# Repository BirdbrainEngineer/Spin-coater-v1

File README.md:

# Birbrain's DIY Spin Coater version 1
This repository contains the source code for a diy spin coater I designed. A video on YouTube showing some of the design- and build process of this device can be found [here](https://www.youtube.com/watch?v=mm2ZiJNfISs). 

### What is it?
 A spin coater is a tool used for depositing thin films of liquids onto a substrate. Usually the liquid is a solution of a relatively quickly evaporating solvent and the coating solute. The phantom force of centrifugal force causes any liquids to travel radially outwards on the substrate. However, due to surface tension, viscocity and other phenomena, some of the solution sticks to the substrate. The solvent from the thin layer of solution then evaporates, leaving behind a thin film of the solute. Using this technique, it is possible to obtain film thicknesses as small as a couple-dozen nanometers!
 
  So... in a nutshell, a spin coater is essentially just a controllable/programmable spinner onto which one can attach a variety of substrates. 
 
### Why?
 Due to the insane simplicity of this device, one would imagine that such tools would be rather cheap and easy to aquire... However, because usually these devices are used in universities and research laboratories, then unfortunately one can expect a markup in the hundreds, to sometimes thousands of percentage points!!! This is just pure insanity, and because I like building some of my own tools, I decided to design and build my own simple spin coater.

 Above is a photo showing thin-film-interference on a coated first-surface mirror(definitely not optical quality haha). The coating solvent was acetone and solute was acrylic, which is a very challenging mix to work with... hence the somewhat sub-par result. 

### Is this project going to be maintained? 
 Don't hold your breath for it! I may upload a few bug fixes if and when they pop up as I work with my spin coater, but I do not intend to improve this version much if at all. There is a likelyhood that a few years from now, I will build a yet more advanced version- a spin coater of laboratory quality for projects that require utmost precision. 

### What is needed to build this project?
The spinner hardware is controlled by a Raspberry-Pi Pico(just Pico from here on), a cheap microcontroller that sits between an Arduino and ESP32 in its processing power. The speed of the Pico as well as its powerful hardware-PWM capabilities are the reason for me picking the Pico for this project.

Multiple extremely important parts of the device, such as the hub and sample holder combo that makes up the gravity chuck design of this spin coater, are meant to be 3d-printed. So, it is basically a necessity to have access to a basic 3d printer... or a cnc mill if going overkill. 

Because I did not make a PCB design for the logic board for this project, then you'll also need access to a soldering station.

And of course, a PC of some sort to be able to compile- and upload the firmware onto the Pico. More on software at [software setup](#software-setup) paragraph of this document.

The list of parts along with their approximate cost can be found at [bill of materials](#bill-of-materials) section of this document. 

## Software setup
This project uses [PlatformIO](https://platformio.org/) with [Visual Studio Code](https://code.visualstudio.com/)(VSCode) IDE. This near-trivializes certain aspects of programming for the Pico. In addition, this project uses the "earlephilhower" Arduino-pico core (see platformio.ini). For these reasons, as far as I am aware, the code is not possible to compile with any other setup, and even if it is possible, I recommend VSCode with PlatformIO anyways. Because the code uses a couple external libraries that PlatformIO normally manages, then it is necessary to have an Internet connection while dealing with this code. 

Getting the firmware for the Pico running should be as simple as these three steps. 

1. Clone the repository to your desired location and open the project in VSCode.
2. Connect the pico to your machine over a usb cable, while holding down the "BOOTSEL" button on the Pico. Release the BOOTSEL button after the Pico is connected.
3. Click "Build" and then "Upload" in VSCode, or just "Upload"(this should automatically build the project). The firmware should then be compiled and uploaded to the Pico. Once VSCode signals to you that the upload is complete, simply unplug the USB from the Pico and on the next power-up of the Pico, it should execute the code of the firmware.

Granted that the rest of the surrounding hardware has been built and set up correctly, the spin coater should just simply work. Surrounding hardware specification can be found under the "[Hardware design](#hardware-design)" paragraph of this document.

## Bill of materials
The prices in the bill of materials are approximate prices of the components that I could quickly find at the time of publishing of this document. These prices are most certainly subject to change over time.

* Anything in brackets is the particular size/component I used.
* Price is for the full amount (eg. 2$ for a component that has 4 stated in the amount, means each component costs 0.50$). 

| Amount | Component                                    | Price  |
|--------|----------------------------------------------|--------|
| 1      | Raspberry Pi Pico                            | 5$     |
| 1      | 80mm 4-pin PC fan (Arctic P8 Max)            | 10$    |
| 1      | 12V, 1A, power adapter with barrel connector | 5$     |
| 1      | SPI micro-SD-card reader module              | 3$     |
| 1      | 16x2 LCD display module                      | 4$     |
| 1      | 4x4 membrane keypad                          | 5$     |
| 1      | 15x21mm KCD1 power switch                    | 1$     |
| 1      | Suitable DC-005 barrel jack (5.5x2.1mm)      | 1$     |
| 4      | Suitable anti-slip rubber furniture leg      | 2$     |
| 1      | 25x (empty) cd/dvd spindle                   | 3$/10$ |
| 2      | WH148 10K potentiometer                      | 2$     |
| 2      | WH148 potentiometer knob                     | 2$     |
| 2      | PT15 10K potentiometer or equivalent         | 0.50$  |
| 12     | 3mm M3 heat set insert                       | 1$     |
| 4      | 4mm M4 heat set insert                       | 1$     |
| 2      | TO220 heatsinks                              | 1$     |
| 16     | M3 10mm screw                                | 0.50$  |
| 4      | M4 20mm or 17mm screw*                       | 0.50$  |
| 1      | 12x8cm prototyping/perf board                | 0.50$  |
| 1      | 1A glass tube fuse                           | 0.50$  |
| 1      | glass tube fuse holder                       | 0.50$  |
| 1      | 1N5819 schottky diode or equivalent          | 0.50$  |
| 5      | 1N4005 diode or equivalent                   | 1$     |
| 2      | 3mm round LED, different colors              | 0.50$  |
| 6      | resistors: 1x1K, 1x4K7, 1x6K8, 2x10K, 1x68K  | 0.50$  |
| 4      | 100nF ceramic capacitor                      | 0.50$  |
| 1      | 330nF 15V+ capacitor(I used 1x100nF, 1x100uF)| 0.50$  |
| 2      | 100uF 15V+ electrolytic capacitor            | 0.50$  |
| 2      | 2N2222A transistor or equivalent             | 0.50$  |
| 1      | F9540N transistor or equivalent              | 1$     |
| 1      | L7805CV voltage regulator                    | 1$     |
| -      | Preferred connectors & wiring for soldering  | ~5$    |
| -      | ~235g of PLA filament                        | 7$     |
| -      | ~42g of PETG filament                        | 1.50$  |

* Total: ~69$

## Hardware design

* Parts with a "*" are technically optional, but recommended. LED-s following a resistor with a * are optional in the same manner. 
* Q3 transistor in the schematic is a BC547A, however this can be replaced with a 2N2222A or equivalent. BC547A is an old and deprecated NPN BJT. The reason why I used it is to have a slower signal fall time (yes, really), which helps to make the PWM duty-cycle look more like what the Pico outputs. With a 2N2222A transistor, the PWM duty cycle to the fan motor is shorter than what the Pico outputs. Technically it should be fine as the PID control loop should be able to compensate.
* R5 & R6 are PT15 type potentiometers. R7 & R8 are WH148 type potentiometers.
* All 1N4005 diodes could technically be replaced by 1N5819 schottky diodes, but should not be necessary. 
* C3 capacity comes from the datasheet for L7805CV, however it does appear that the capacity can be larger. Probably the more important thing is that at least some of the capacity is quick-acting, eg. ceramic capacitors. 

### Some notes on the design...
If you would prefer to use a KiCAD schematic, then one has been produced and tested by @krasimirk. It can be found in the [BirdbrainSpinCoaterPCB_v1.1 directory](Hardware/BirdbrainSpinCoaterPCB_v1.1).

Make sure to install a TO-220 heatsink at least on the L7805CV, it will burn out otherwise. A heatsink on the F9540N is technically not needed, but optional.

One might notice that the 16x2 LCD display is directly interfaced with the Pico, even though the LCD display is running off 5V. This is safe to do as long as RW is tied to ground, guaranteeing that the display only ever gets written to. In such a case, the Pico's 3.3V should be enough to count as a logical high while transmitting data. 

## Spinner usage
If you have built yourself a spin coater of this design and firmware then here's a rundown of what can be found in the menu system of the spinner and what the different options do. 

### Keys
By default the keymapping for the spin coater when using the default 4x4 membrane keypad is as follows:

* Numerics - Correspond to the corresponding number. 
* `*` - Backspace / Exit.
* `#` - Enter / OK.
* `A` - YES, if a question prompt appears; Otherwise the letter A.
* `B` - NO, if a question prompt appears; Otherwise the letter B.
* `C` - UP, if navigating the menus; Otherwise the letter C.
* `D` - DOWN, if navigating the menus; Decimal dot/period ( `.` ), if entering a fractional number; Otherwise the letter D. 

### Booting
*For a painless first boot of the spin coater, make sure to copy the contents of the "Spinner Memory Image" folder onto a clean SD card. Ideally the SD card has a relatively small memory size.*

During booting, the spin coater checks for whether an SD card can be found on the default SPI pins. If not, then the spin coater will enter [memoryless operation](#memoryless-operation), and notifies the user of this occuring. The menu should then appear and the spin coater is ready for use in memoryless operation mode. 

If the SD card is present, then next the spin coater will check whether a `JOBS` folder exists in the root directory of the SD card. If not, one will be created automatically. If the `JOBS` folder exists, then the spin coater will attempt to load any jobs in the folder. The `JOBS` folder should contain *only* job files. [Job files](#job-file-structure) are extensionless JSON files with a very specific structure. Errors during this phase of booting could end up being unrecoverable AND recurring. If this is the case, the spin coater should be shut down, after which the SD card has to be removed from the spin coater and the files inspected at a PC. Any job files that have been saved incorrectly should be deleted from the folder. The spin coater should be able to boot again after doing so. 

Next the spin coater will attempt to locate the PID test job file called `PID` in the root directory. If this job is not found or is corrupted, then the spin coater will not be able to use the "PID test" functionality. In case of this happening and the user still wanting to use the PID test functionality, the user should shut down the spin coater, then remove the SD card from the spin coater and inspect the files at a PC. If a file called `PID` exists in the root directory then the integrity of the file should be checked, or alternatively a new PID test job file should replace the corrupted one. If the file is missing then a job has to be created/copied, and the file renamed to `PID`. 

### Normal operation
* `1/5: Quick start`
    * `1/2: Programmed` - Opens up a standard [job routine creation](#job-routine-creation) dialouge. After the dialouge has been finished, asks whether to run the job or not. If answered affirmatively, then executes the programmed job routine. After the routine has finished, asks whether to run the job again or not. If answered affirmatively, runs the job again. Otherwise asks whether to store the job permanently. If answered affirmatively, then a job name can be entered and the job routine will be saved as a job that can be interacted with through the `Jobs` menu.  
    * `2/2: Analog` - Gives direct control over the spinner to the user. The speed can be adjusted using the "coarse" and "fine" potentiometers. Coarse control spans from 0% to 90% of maximum spinner speed. Fine control spans a 10% range that gets added ontop of the current coarse control. Eg. if coarse control is set to 38% and fine control to 4%, then the output speed will be 42% of the maximum spinner speed. **WARNING: When exiting analog control mode, the spinner spins up to a slow speed for a few seconds, even if the spinner is already stationary!**
* `2/5: Jobs`
    * `1/3: Load job` - Opens a list of jobs currently stored on the SD card. The specific job can be searched in the menu, or by using the `Search for a job` function. If the job search turns up positive or the specific job is chosen from the menu, the spin coater asks whether to run the job. If answered affirmatively, performs the job routine. 
    * `2/3: Create job` - First asks to enter the new job routine's name. If a job with the specified name already exists, then offers to enter a different name or delete the job with the specified name. Once a suitable name is chosen, the spin coater asks to confirm the name, after which the standard [job routine creation](#job-routine-creation) dialouge is opened. After the job routine is finished, the job is saved on the SD card. If the user decided to override a previous job, then the previous job with the same name is deleted before the new job is saved. 
    * `3/3: Delete job` - Opens a list of jobs stored on the SD card. The specific job the user wishes to delete can be searched in the menu, or by using the `Search for a job` function. When answered affirmatively to whether to really delete the specified job, the job is removed deleted from the SD card. **As it stands right now, the "Search for a job" option is rather buggy, so it is not recommended to use it!**
* `3/5: Test`
    * `1/2: Spinner params.` - Spinner parameters test is a rudimentary test to find out some basic parameters of the spinner. The test consists of a speed- and acceleration tests. The speed test finds out the minimum and maximum speed of the spinner, as well as the minimum duty cycle length to make the spinner spin. The acceleration test tests the maximum acceleration and deceleration three times in a row, and then averages the results. The results from the tests are then displayed to the user to create their job routines accordingly. The minimum duty cycle speed will not be reported to the user but the spin coater's configuration is updated accordingly. **Please note that since the very first test is finding out the minimum duty cycle of the spinner, it may look like nothing is happening for a while. Rest assured, the controller is simply creeping up on the minimum duty cycle.**
    * `2/2: PID` - PID test is a rudimentary test to gauge whether the current PID constants are performing acceptably. The routine of this test can be changed by manually replacing the job file named `PID` in the root directory on the SD card. 
* `4/5: Calibration`
    * `1/6: Set Kp` - Displays the currently set P (proportional) constant of the PID controller. If no numeric value is entered, the constant remains unchanged, otherwise new number is set as the new value of the constant. The configuration of the spin coater is also updated so on next "normal operation" boot the constant is retained. 
    * `2/6: Set Ki` - Displays the currently set I (integral) constant of the PID controller. If no numeric value is entered, the constant remains unchanged, otherwise new number is set as the new value of the constant. The configuration of the spin coater is also updated so on next "normal operation" boot the constant is retained. 
    * `3/6: Set Kd` - Displays the currently set D (derivative) constant of the PID controller. If no numeric value is entered, the constant remains unchanged, otherwise new number is set as the new value of the constant. The configuration of the spin coater is also updated so on next "normal operation" boot the constant is retained. 
    * `4/6: Min duty cycle` - Updates the configuration of the spin coater to reflect the new minimum duty cycle value obtained during the last "Spinner parameters" test. Effect is immediate.
    * `5/6: Analog-in alpha` - Allows for adjusting the alpha of the exponential average for the analog control potentiometer readings. Should be a value between `0` and `1` (default is `0.01`). Smaller values mean the average, and therefore the whole reading of the potentiometers moves slower, but noise in the readings is suppressed. **Changing this value is unlikely to be needed.**
    * `6/6 RPM alpha` - Allows for adjusting the alpha of the exponential average for the RPM readings. Should be a value between `0` and `1`(default is `0.2`). Smaller values mean the average, and therefore the whole reading of the potentiometers moves slower, but noise in the readings is suppressed. **Changing this value is unlikely to be needed.**
* `5/5: Information`
    * `1/3: Device info.` - Device information contains the current revision of the firmware and hardware, programmer names/handles and hardware developer names/handles, as well as the software- and hardware license identifiers.
    * `2/3: HARDWARE LICENSE` - Embedded license identifier and link for more information about the Creative Commons 4.0 Attribution-ShareAlike license.
    * `3/3: SOFTWARE LICENSE` - Embedded MIT license.

### Memoryless operation
In memoryless operation mode the spin coater is not able to execute any functionality that has to do with accessing the memory, naturally. 

If `Programmed` is chosen from first menu option `Quick start`, then the spin coater will not offer to save the created set of instructions as a job when exiting the `Programmed` mode. 

The second menu option `Jobs` is completely non-functional. 

The "PID test" under third menu option `Test` is not available.

All spinner configuration will have reverted back to firmware defaults. It is possible to update the configuration, however if the spin coater is shut down, all changes made are lost.

## Building your own
If you would like to build your own spin coater of this design, then the [assembly manual](https://birdbrain.engineer/spin-coater/instructions/) can be found in the **Instructions** folder of this repository.

## Licenses
The software of this project is licensed under [MIT](https://opensource.org/license/mit/) software license.

The hardware design of this project is licensed under [Creative Commons 4.0 Attribution-ShareAlike](https://creativecommons.org/licenses/by-sa/4.0/deed.en) license.

## Job routine creation

When creating a job routine in the spinner, the spinner will ask the following three questions in a loop.

1. **Which task to perform** 
    
    * *Ramp* - Performs a linear ramp-up or ramp-down of the speed of the spinner.
    * *Hold* - Holds the spinner speed at a specified speed.
    * *End* - Final instruction in a job routine, if this is encountered, the job routine is immediately stopped and finished.

2. **RPM / Speed**
    
    If the task was to "ramp", then it will linearly interpolate towards this speed from the previously set speed (0 if first task in the routine). If the task was "hold", then sets the speed setpoint to this speed. No effect if any other task is encountered.

3. **Duration**

    The duration of the particular task in the routine in **milliseconds**. In case of "ramp" task, the speed is interpolated over the course of this time duration. In case of "hold" task, the speed is set and held for this time duration. No effect if any other task is encountered.

Once the `End` task is chosen while programming a job routine, the spin coater will immediately assume the job routine finished and so the programming interface is exited.

For example, if the following commands are entered while programming:

* Ramp, 3000, 5000
* Hold, 3000, 5000
* Ramp, 500, 6000
* End

... then when the job gets executed, the spin coater would linearly spin the spinner from 0 RPM up to 3000RPM over the course of 5 seconds. It would then hold the speed at 3000RPM for a further 5 seconds. Finally, it would linearly slow down the spinner from 3000RPM to 500RPM over the course of 6 seconds. The job would then immediately finish. 

## Job file structure
Job files are [JSON](https://www.json.org/json-en.html) files with no `.json` extension.

To have the spin coater load your job files, they need to be placed into the `JOBS` folder which should be found in the root directory of the SD card. The only exception to this is the job file called `PID`, which is used for the PID test. The `PID` job should be found in the root directory of the SD card.

The following is a sample job file.

The job file has 5 single-valued variables and a single array.

* `length` is an integer that **must** be equal to the number of elements in the `sequence` array.
* `use_embedded_pid_constants` is a boolean which specifies whether to use the `Kp`, `Ki` and `Kd` values baked into the job file as PID constants for the PID controller, or whether to use the spinner's currently set internal PID constants. `false` means that the spinner's internal PID constants are used instead of the constants specified in the file.
* `Kp` is a floating point number that will be used as the **Kp** constant for the PID controller if `use_embedded_pid_constants` is set to `true`. 
* `Ki` is a floating point number that will be used as the **Ki** constant for the PID controller if `use_embedded_pid_constants` is set to `true`. 
* `Kd` is a floating point number that will be used as the **Kd** constant for the PID controller if `use_embedded_pid_constants` is set to `true`. 
* `sequence` is an array type which holds elements made of three variables:
    * `duration` is an integer. Refer to [job routine creation](#job-routine-creation) for more information.
    * `task` is an integer. `1` means "hold" task, `2` means "ramp" task and `3` means "end" task. No other numbers should be used here. Refer to [job routine creation](#job-routine-creation) for more information.
    * `rpm` is an integer. Refer to [job routine creation](#job-routine-creation) for more information.

## Known bugs
* The `Search for a job` functionality under `Delete job` menu does not work properly if the name contains numbers. **Workaround:** Find the job you wish to delete in the `Delete job` menu manually and delete it that way.

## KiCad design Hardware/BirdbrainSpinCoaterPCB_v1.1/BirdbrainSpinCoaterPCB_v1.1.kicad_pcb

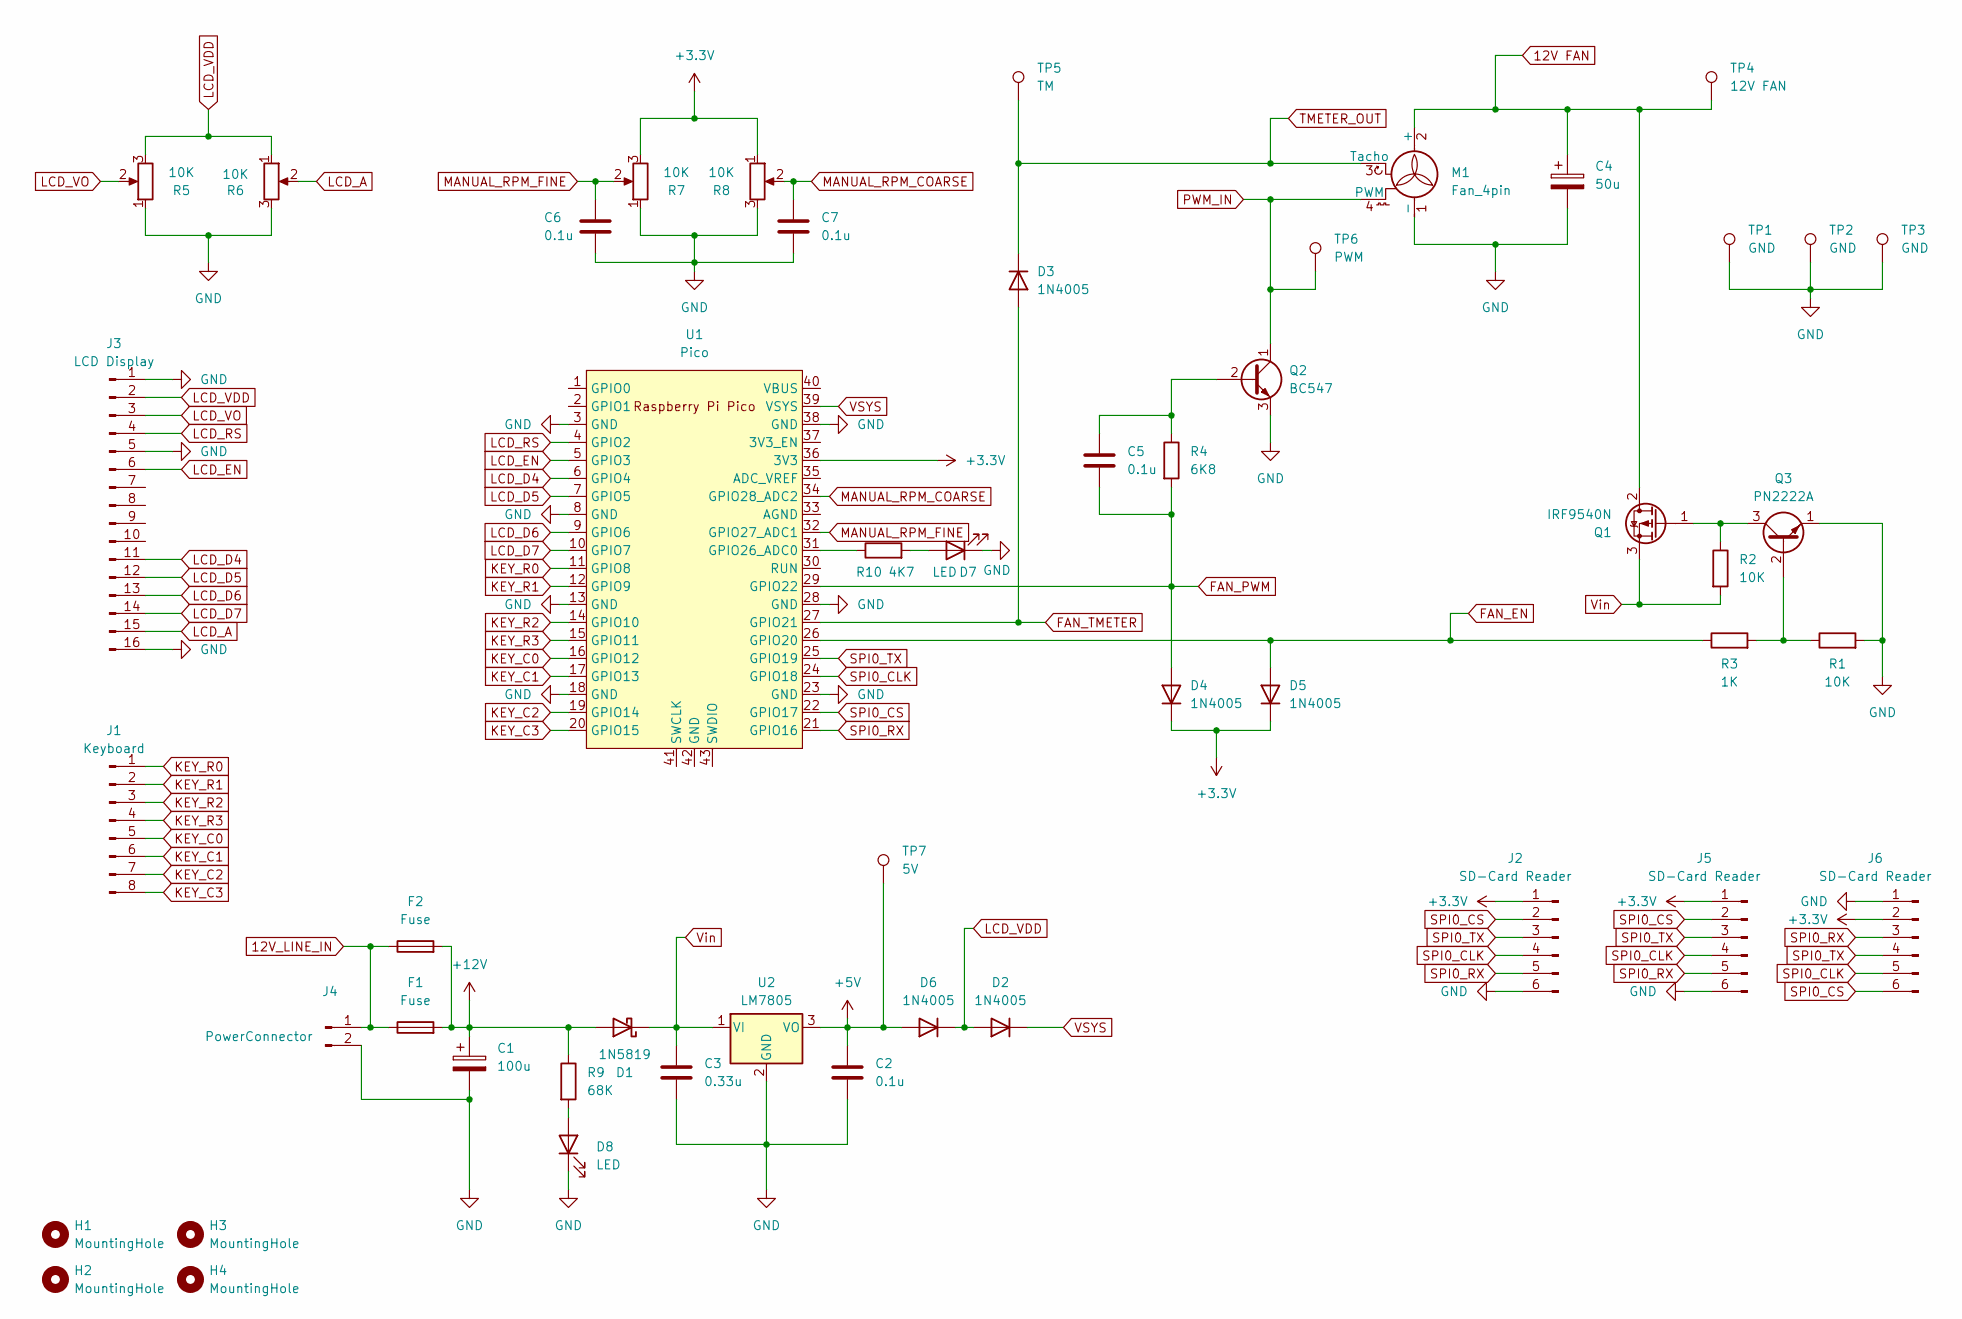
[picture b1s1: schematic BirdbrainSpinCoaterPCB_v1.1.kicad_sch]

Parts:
C1: 100u; CP_Radial_D5.0mm_P2.00mm
C2, C5, C6, C7: 0.1u; DualFootprint_C1206_Radial
C3: 0.33u; DualFootprint_C1206_Radial
C4: 50u; CP_Radial_D5.0mm_P2.00mm
D1: 1N5819; D_DO-41_SOD81_SOD123_P10.16mm_Horizontal
D2, D3, D4, D5, D6: 1N4005; D_DO-41_SOD81_SOD123_P10.16mm_Horizontal
D7, D8: LED; LED_D5.0mm
F1: Fuse; Fuseholder_Clip-5x20mm_Littelfuse_100_Inline_P20.50x4.60mm_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
F2: Fuse; Fuse_1210_3225Metric
H1, H2, H3, H4: MountingHole; MountingHole_3.2mm_M3
J1: Keyboard; PinHeader_1x08_P2.54mm_Vertical
J2, J5, J6: SD-Card Reader; PinHeader_1x06_P2.54mm_Vertical
J3: LCD Display; PinHeader_1x16_P2.54mm_Vertical
J4: PowerConnector; TerminalBlock_Phoenix_MKDS-1,5-2-5.08_1x02_P5.08mm_Horizont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
M1: Fan_4pin; PinHeader_1x04_P2.54mm_Vertical
Q1: IRF9540N; TO-220-3_Vertical
Q2: BC547; TO-92_Dual
Q3: PN2222A; TO-92_Dual
R1, R2: 10K; DualFootprint_R1206_Axial7.62
R3: 1K; DualFootprint_R1206_Axial7.62
R4: 6K8; DualFootprint_R1206_Axial7.62
R5, R6, R7, R8: 10K; Potentiometer_Bourns_3296W_Vertical
R9: 68K; DualFootprint_R1206_Axial7.62
R10: 4K7; DualFootprint_R1206_Axial7.62
TP1, TP2, TP3: GND; PinHeader_1x01_P2.54mm_Vertical
TP4: 12V FAN; PinHeader_1x01_P2.54mm_Vertical
TP5: TM; PinHeader_1x01_P2.54mm_Vertical
TP6: PWM; PinHeader_1x01_P2.54mm_Vertical
TP7: 5V; PinHeader_1x01_P2.54mm_Vertical
U1: Pico; RPi_Pico_SMD_TH
U2: LM7805; TO-220-3_Vertical

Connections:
12V FAN: C4.1, M1.2 (+), Q1.2 (D), TP4.1
12V_LINE_IN: F1.1, F2.1, J4.1
+3.3V: D4.1 (K), D5.1 (K), J2.1, J5.1, J6.2, R7.3, R8.1, U1.36 (3V3)
+5V: C2.1, D6.2 (A), TP7.1, U2.3 (VO)
+12V: C1.1, D1.2 (A), F1.2, F2.2, R9.1
FAN_EN: D5.2 (A), R3.1, U1.26 (GPIO20)
FAN_PWM: C5.2, D4.2 (A), R4.2, U1.29 (GPIO22)
FAN_TMETER: D3.2 (A), U1.27 (GPIO21)
GND: C1.2, C2.2, C3.2, C4.2, C6.2, C7.2, D7.1 (K), D8.1 (K), J2.6, J3.1, J3.5, J3.16, J4.2, J5.6, J6.1, M1.1 (-), Q2.3 (E), Q3.1 (E), R1.2, R5.1, R6.3, R7.1, R8.3, TP1.1, TP2.1, TP3.1, U1.3 (GND), U1.8 (GND), U1.13 (GND), U1.18 (GND), U1.23 (GND), U1.28 (GND), U1.38 (GND), U2.2 (GND)
KEY_C0: J1.5, U1.16 (GPIO12)
KEY_C1: J1.6, U1.17 (GPIO13)
KEY_C2: J1.7, U1.19 (GPIO14)
KEY_C3: J1.8, U1.20 (GPIO15)
KEY_R0: J1.1, U1.11 (GPIO8)
KEY_R1: J1.2, U1.12 (GPIO9)
KEY_R2: J1.3, U1.14 (GPIO10)
KEY_R3: J1.4, U1.15 (GPIO11)
LCD_A: J3.15, R6.2
LCD_D4: J3.11, U1.6 (GPIO4)
LCD_D5: J3.12, U1.7 (GPIO5)
LCD_D6: J3.13, U1.9 (GPIO6)
LCD_D7: J3.14, U1.10 (GPIO7)
LCD_EN: J3.6, U1.5 (GPIO3)
LCD_RS: J3.4, U1.4 (GPIO2)
LCD_VDD: D2.2 (A), D6.1 (K), J3.2, R5.3, R6.1
LCD_VO: J3.3, R5.2
MANUAL_RPM_COARSE: C7.1, R8.2, U1.34 (GPIO28_ADC2)
MANUAL_RPM_FINE: C6.1, R7.2, U1.32 (GPIO27_ADC1)
unnamed: D7.2 (A), R10.2
unnamed: D8.2 (A), R9.2
unnamed: Q1.1 (G), Q3.3 (C), R2.1
unnamed: C5.1, Q2.2 (B), R4.1
unnamed: Q3.2 (B), R1.1, R3.2
unnamed: R10.1, U1.31 (GPIO26_ADC0)
PWM_IN: M1.4 (PWM), Q2.1 (C), TP6.1
SPI0_CLK: J2.4, J5.4, J6.5, U1.24 (GPIO18)
SPI0_CS: J2.2, J5.2, J6.6, U1.22 (GPIO17)
SPI0_RX: J2.5, J5.5, J6.3, U1.21 (GPIO16)
SPI0_TX: J2.3, J5.3, J6.4, U1.25 (GPIO19)
TMETER_OUT: D3.1 (K), M1.3 (Tacho), TP5.1
VSYS: D2.1 (K), U1.39 (VSYS)
Vin: C3.1, D1.1 (K), Q1.3 (S), R2.2, U2.1 (VI)

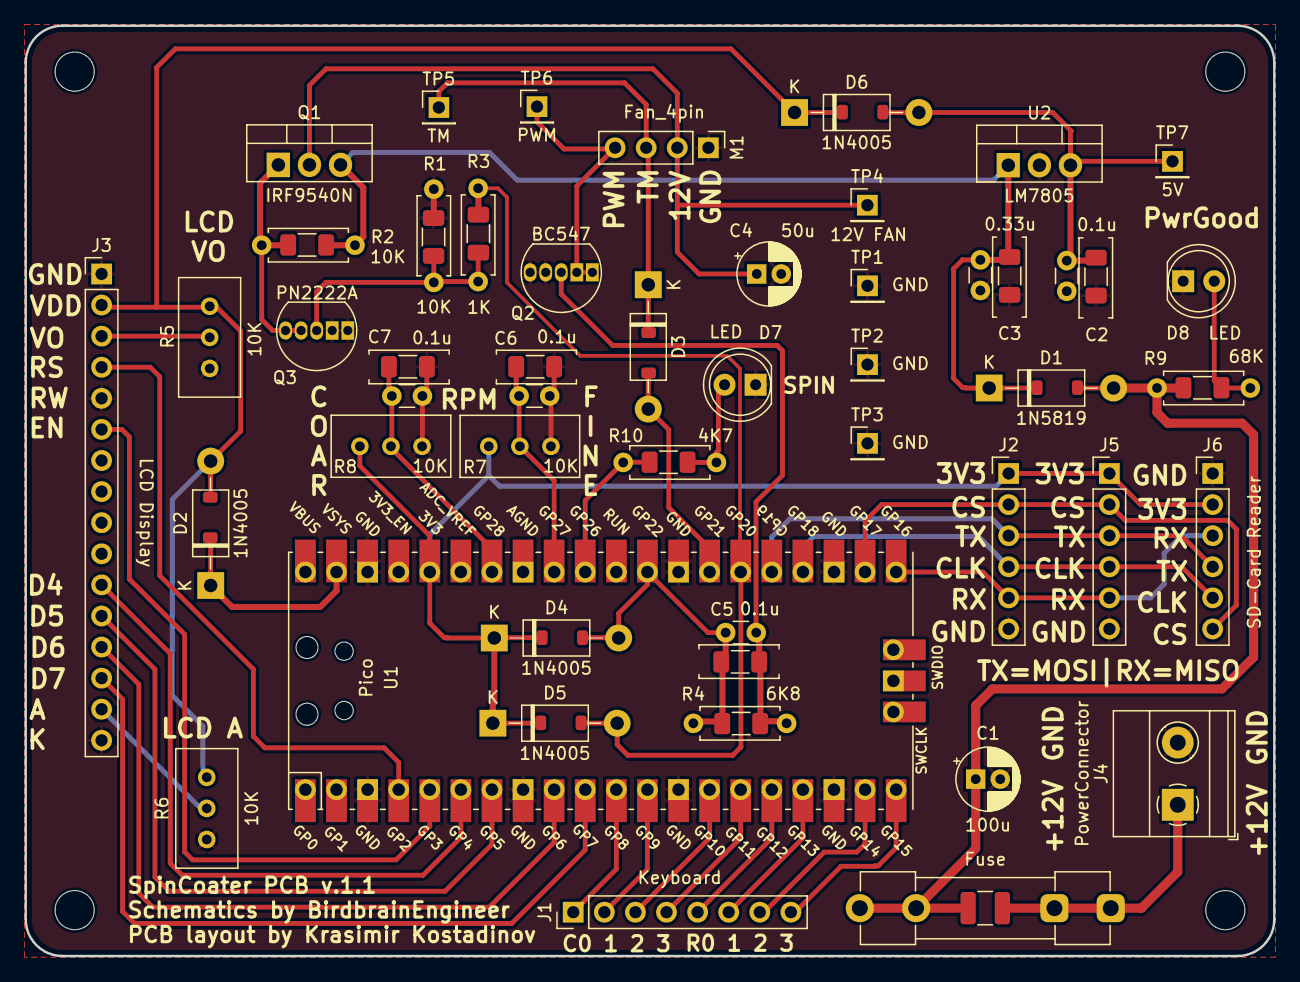
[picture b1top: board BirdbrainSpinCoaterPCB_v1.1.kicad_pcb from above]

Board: 2 copper layers, 102.0 x 76.0 mm, 50 parts (0 on the bottom side), 42 nets.

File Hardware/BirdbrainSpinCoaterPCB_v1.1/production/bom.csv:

Designator,Footprint,Quantity,Value,LCSC Part #
C1,CP_Radial_D5.0mm_P2.00mm,1,100u,
"C2, C5, C6, C7",DualFootprint_C1206_Radial,4,0.1u,
C3,DualFootprint_C1206_Radial,1,0.33u,
C4,CP_Radial_D5.0mm_P2.00mm,1,50u,
D1,D_DO-41_SOD81_SOD123_P10.16mm_Horizontal,1,1N5819,
"D2, D3, D4, D5, D6",D_DO-41_SOD81_SOD123_P10.16mm_Horizontal,5,1N4005,
"D7, D8",LED_D5.0mm,2,LED,
F1,Fuseholder_Clip-5x20mm_Littelfuse_100_Inline_P20.50x4.60mm_D1.30mm_Horizontal,1,Fuse,
F2,1210,1,Fuse,
J1,PinHeader_1x08_P2.54mm_Vertical,1,Keyboard,
"J2, J5, J6",PinHeader_1x06_P2.54mm_Vertical,3,SD-Card Reader,
J3,PinHeader_1x16_P2.54mm_Vertical,1,LCD Display,
J4,"TerminalBlock_Phoenix_MKDS-1,5-2-5.08_1x02_P5.08mm_Horizontal",1,PowerConnector,
M1,PinHeader_1x04_P2.54mm_Vertical,1,Fan_4pin,
Q1,TO-220-3_Vertical,1,IRF9540N,
Q2,TO-92_Dual,1,BC547,
Q3,TO-92_Dual,1,PN2222A,
"R1, R2",DualFootprint_R1206_Axial7.62,2,10K,
R10,DualFootprint_R1206_Axial7.62,1,4K7,
R3,DualFootprint_R1206_Axial7.62,1,1K,
R4,DualFootprint_R1206_Axial7.62,1,6K8,
"R5, R6, R7, R8",Potentiometer_Bourns_3296W_Vertical,4,10K,
R9,DualFootprint_R1206_Axial7.62,1,68K,
"TP1, TP2, TP3",PinHeader_1x01_P2.54mm_Vertical,3,GND,
TP4,PinHeader_1x01_P2.54mm_Vertical,1,12V FAN,
TP5,PinHeader_1x01_P2.54mm_Vertical,1,TM,
TP6,PinHeader_1x01_P2.54mm_Vertical,1,PWM,
TP7,PinHeader_1x01_P2.54mm_Vertical,1,5V,
U1,RPi_Pico_SMD_TH,1,Pico,
U2,TO-220-3_Vertical,1,LM7805,

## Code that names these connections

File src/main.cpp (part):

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// Make sure to set the pinout for your implementation! Do not change the pin variable names!
// 0 used for usb, I think
// 1 used for usb, I think...?
const int lcd_rs = 2;
const int lcd_en = 3;
#if HW_REVISION == 1
const int lcd_d4 = 5;
const int lcd_d5 = 4;
#else
const int lcd_d4 = 4; 
const int lcd_d5 = 5;
#endif
const int lcd_d6 = 6;
const int lcd_d7 = 7;
const int membrane_row_0_pin = 8;
const int membrane_row_1_pin = 9;
const int membrane_row_2_pin = 10;
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const int membrane_col_2_pin = 14;
const int membrane_col_3_pin = 15;
//=====================
const int SPI0_RX = 16;  //Do not change! Arduino-pico core default pin, used for SD card reader
const int SPI0_SC = 17;  //Do not change! Arduino-pico core default pin, used for SD card reader
const int SPI0_CLK = 18; //Do not change! Arduino-pico core default pin, used for SD card reader
const int SPI0_TX = 19;  //Do not change! Arduino-pico core default pin, used for SD card reader
const int spinner_power_enable_pin = 20;
const int tachometer_pin = 21;
const int motor_pwm_pin = 22;
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
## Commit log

2023-10-06 Start adding core
2023-10-06 Added TextBuffer
2023-10-07 Start implementation of Menu system
2023-10-07 Add JSON parsing capability
2023-10-07 First implementation of job system
2023-10-08 Add Software timer capability
2023-10-09 Make the linker behave
2023-10-09 Menu system theoretically complete
2023-10-09 Menu system working
2023-10-11 JobTable created
2023-10-18 Progress on functionality
2023-10-18 Add more core functionality
2023-10-21 First full firmware complete
2023-10-27 Grand bug fixing
2023-10-27 Improve spinner usability
2023-10-28 Memoryless operation, bugfixes & small improvements
2023-10-28 Version 0.1.0
2023-11-24 Last adjustments
2023-11-24 Add documentation and design files
2023-11-25 Ready for video shoot
2023-11-25 Update video link
2023-11-25 Add missing Spinner Memory Image
2023-11-28 Replace file with correct SD card slot spacing
2023-11-30 Add assembly manual and finish README
2023-11-30 Update assembly instruction link
2025-09-21 Fix 0 RPM bug, add serial debug
2025-12-02 Add KiCAD schematic by @krasimirk
2025-12-02 Update README with KiCAD schematic details

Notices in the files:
src/main.cpp:
Copyright 2023 Birdbrain
README.md:
Licenses:
The software of this project is licensed under [MIT](https://opensource.org/license/mit/) software license.
The hardware design of this project is licensed under [Creative Commons 4.0 Attribution-ShareAlike](https://creativecommons.org/licenses/by-sa/4.0/deed.en) license.
`1/3: Device info.` - Device information contains the current revision of the firmware and hardware, programmer names/handles and hardware developer names/handles, as well as the software- and hardware license identifiers.
